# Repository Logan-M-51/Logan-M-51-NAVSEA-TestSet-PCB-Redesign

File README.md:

# Logan-M-51-NAVSEA-TestSet-PCB-Redesign
This project was completed as a senior design project as one of the graduation requirements for the Computer Engineering and Systems
program at the university of Washington Tacoma. 
This particular project was sponsored by NAVSEA, and completed with a group of three students.

This assignment was given to UWT students to extend the lifespan of the detonator test set circuitry shelf life. 
The current solution is over half a century old and is experiencing more failures as time goes on.
Thus, this redesign mimics the same functionality of the original test set while in a PCB format.
This allows NAVSEA engineers to replace the components in use withouth having to retrain test set operators.

Solution was tested in LTSpice, as well as on breadboard recreations.

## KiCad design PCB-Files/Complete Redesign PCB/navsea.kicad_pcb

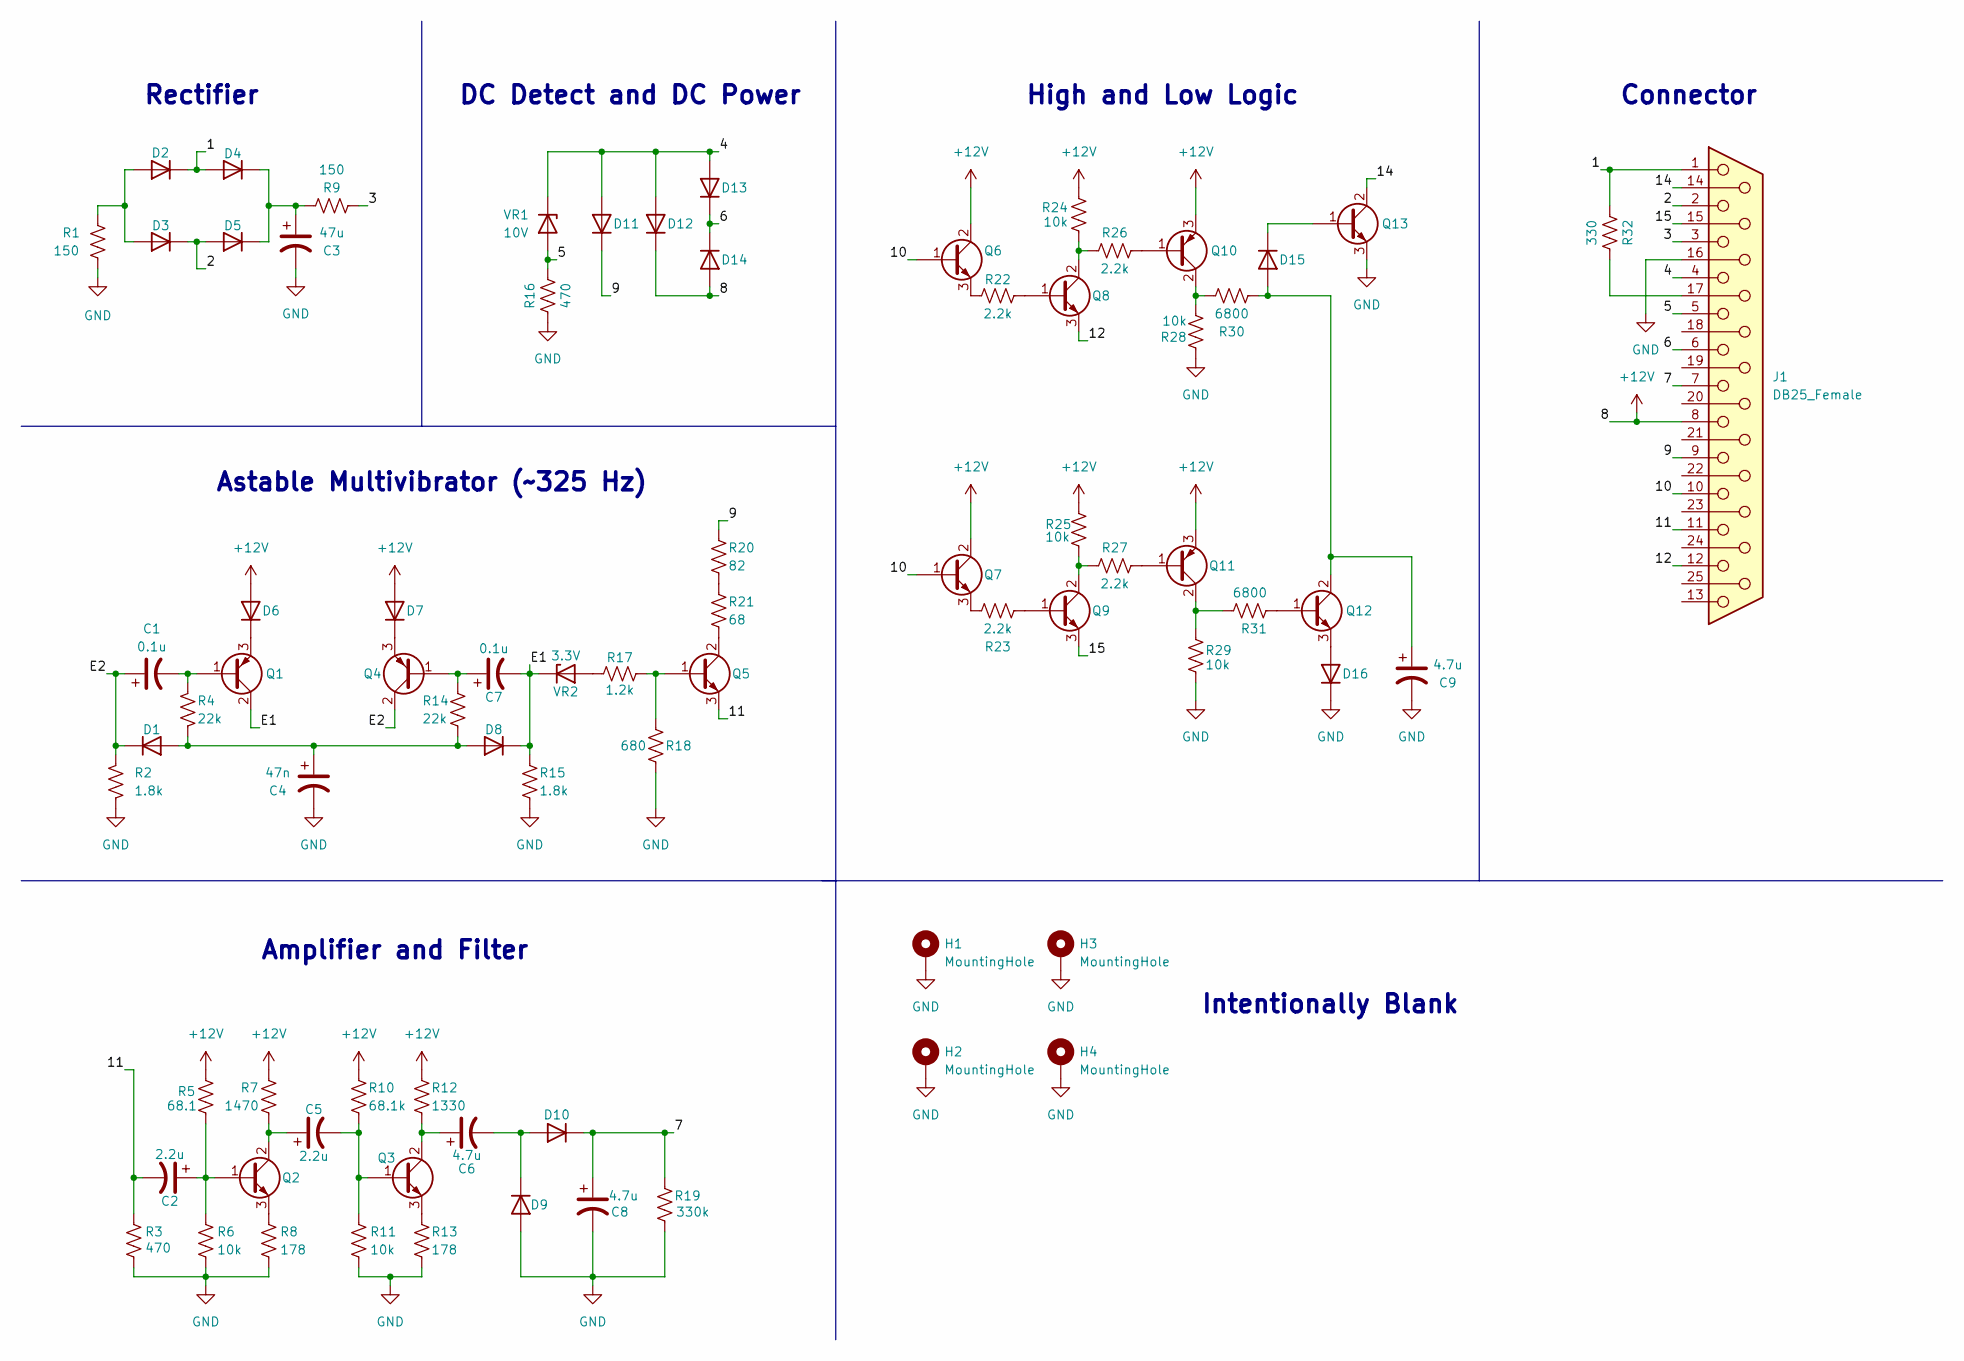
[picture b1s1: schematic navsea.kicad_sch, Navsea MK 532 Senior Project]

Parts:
C1, C7: 0.1u; CP_Radial_Tantal_D4.5mm_P2.50mm
C2, C5: 2.2u; CP_Radial_Tantal_D4.5mm_P2.50mm
C3: 47u; CP_Radial_D8.0mm_P3.50mm
C4: 47n; C_Axial_L5.1mm_D3.1mm_P10.00mm_Horizontal
C6: 4.7u; CP_Radial_D8.0mm_P3.50mm
C8, C9: 4.7u; CP_Axial_L10.0mm_D4.5mm_P15.00mm_Horizontal
D1, D2, D3, D4, D5, D6, D7, D8, D9, D10, D11, D12, D13, D14, D15, D16: D; D_DO-41_SOD81_P7.62mm_Horizontal
H1, H2, H3, H4: MountingHole; MountingHole_4.3mm_M4_Pad_Via
J1: DB25_Female; DSUB-25_Female_Horizontal_P2.77x2.84mm_EdgePinOffset4.94mm_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
Q1, Q4, Q10, Q11: PNP; TO-18-3
Q2, Q3, Q5, Q6, Q7, Q8, Q9, Q12, Q13: Q_NPN_BCE; TO-18-3
R1, R9: 150; R_Axial_DIN0414_L11.9mm_D4.5mm_P15.24mm_Horizontal
R2, R15: 1.8k; R_Axial_DIN0207_L6.3mm_D2.5mm_P7.62mm_Horizontal
R3, R16: 470; R_Axial_DIN0207_L6.3mm_D2.5mm_P7.62mm_Horizontal
R4, R14: 22k; R_Axial_DIN0207_L6.3mm_D2.5mm_P7.62mm_Horizontal
R5: 68.1; R_Axial_DIN0207_L6.3mm_D2.5mm_P7.62mm_Horizontal
R6, R11, R24, R25, R28, R29: 10k; R_Axial_DIN0207_L6.3mm_D2.5mm_P7.62mm_Horizontal
R7: 1470; R_Axial_DIN0207_L6.3mm_D2.5mm_P7.62mm_Horizontal
R8, R13: 178; R_Axial_DIN0207_L6.3mm_D2.5mm_P7.62mm_Horizontal
R10: 68.1k; R_Axial_DIN0207_L6.3mm_D2.5mm_P7.62mm_Horizontal
R12: 1330; R_Axial_DIN0207_L6.3mm_D2.5mm_P7.62mm_Horizontal
R17: 1.2k; R_Axial_DIN0207_L6.3mm_D2.5mm_P7.62mm_Horizontal
R18: 680; R_Axial_DIN0207_L6.3mm_D2.5mm_P7.62mm_Horizontal
R19: 330k; R_Axial_DIN0207_L6.3mm_D2.5mm_P7.62mm_Horizontal
R20: 82; R_Axial_DIN0207_L6.3mm_D2.5mm_P7.62mm_Horizontal
R21: 68; R_Axial_DIN0207_L6.3mm_D2.5mm_P7.62mm_Horizontal
R22, R23, R26, R27: 2.2k; R_Axial_DIN0207_L6.3mm_D2.5mm_P7.62mm_Horizontal
R30, R31: 6800; R_Axial_DIN0207_L6.3mm_D2.5mm_P7.62mm_Horizontal
R32: 330; R_Axial_DIN0207_L6.3mm_D2.5mm_P7.62mm_Horizontal
VR1: 10V; D_DO-41_SOD81_P7.62mm_Horizontal
VR2: 3.3V; D_DO-35_SOD27_P7.62mm_Horizontal

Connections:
+12V: D6.2 (A), D7.2 (A), D12.1 (K), D14.2 (A), J1.8, Q6.2 (C), Q7.2 (C), Q10.3 (E), Q11.3 (E), R5.1, R7.1, R10.1, R12.1, R24.1, R25.1
/1: D2.1 (K), D4.2 (A), J1.1, R32.2
/2: D3.1 (K), D5.2 (A), J1.2
/3: J1.3, R9.1
/4: D11.2 (A), D12.2 (A), D13.2 (A), J1.4, VR1.1 (K)
/5: J1.5, R16.2, VR1.2 (A)
/6: D13.1 (K), D14.1 (K), J1.6
/7: C8.1, D10.1 (K), J1.7, R19.1
/9: D11.1 (K), J1.9, R20.1
/10: J1.10, Q6.1 (B), Q7.1 (B)
/11: C2.2, J1.11, Q5.3 (E), R3.1
/12: J1.12, Q8.3 (E)
/14: J1.14, Q13.2 (C)
/15: J1.15, Q9.3 (E)
/E1: C7.2, D8.1 (K), Q1.2 (C), R15.1, VR2.1 (K)
/E2: C1.1, D1.1 (K), Q4.2 (C), R2.1
GND: C3.2, C4.2, C8.2, C9.2, D9.2 (A), D16.1 (K), H1.1, H2.1, H3.1, H4.1, J1.16, Q13.3 (E), R1.2, R2.2, R3.2, R6.2, R8.2, R11.2, R13.2, R15.2, R16.1, R18.1, R19.2, R28.2, R29.2
unnamed: C1.2, Q1.1 (B), R4.1
unnamed: C2.1, Q2.1 (B), R5.2, R6.1
unnamed: C3.1, D4.1 (K), D5.1 (K), R9.2
unnamed: C4.1, D1.2 (A), D8.2 (A), R4.2, R14.2
unnamed: C5.1, Q2.2 (C), R7.2
unnamed: C5.2, Q3.1 (B), R10.2, R11.1
unnamed: C6.1, Q3.2 (C), R12.2
unnamed: C6.2, D9.1 (K), D10.2 (A)
unnamed: C7.1, Q4.1 (B), R14.1
unnamed: C9.1, D15.2 (A), Q12.2 (C), R30.1
unnamed: D2.2 (A), D3.2 (A), R1.1
unnamed: D6.1 (K), Q1.3 (E)
unnamed: D7.1 (K), Q4.3 (E)
unnamed: D15.1 (K), Q13.1 (B)
unnamed: D16.2 (A), Q12.3 (E)
unnamed: J1.17, R32.1
unnamed: Q2.3 (E), R8.1
unnamed: Q3.3 (E), R13.1
unnamed: Q5.1 (B), R17.2, R18.2
unnamed: Q5.2 (C), R21.2
unnamed: Q6.3 (E), R22.1
unnamed: Q7.3 (E), R23.1
unnamed: Q8.1 (B), R22.2
unnamed: Q8.2 (C), R24.2, R26.1
unnamed: Q9.1 (B), R23.2
unnamed: Q9.2 (C), R25.2, R27.1
unnamed: Q10.1 (B), R26.2
unnamed: Q10.2 (C), R28.1, R30.2
unnamed: Q11.1 (B), R27.2
unnamed: Q11.2 (C), R29.1, R31.1
unnamed: Q12.1 (B), R31.2
unnamed: R17.1, VR2.2 (A)
unnamed: R20.2, R21.1

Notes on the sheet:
Rectifier
Connector
DC Detect and DC Power
Amplifier and Filter
Intentionally Blank
High and Low Logic
Astable Multivibrator (~325 Hz)

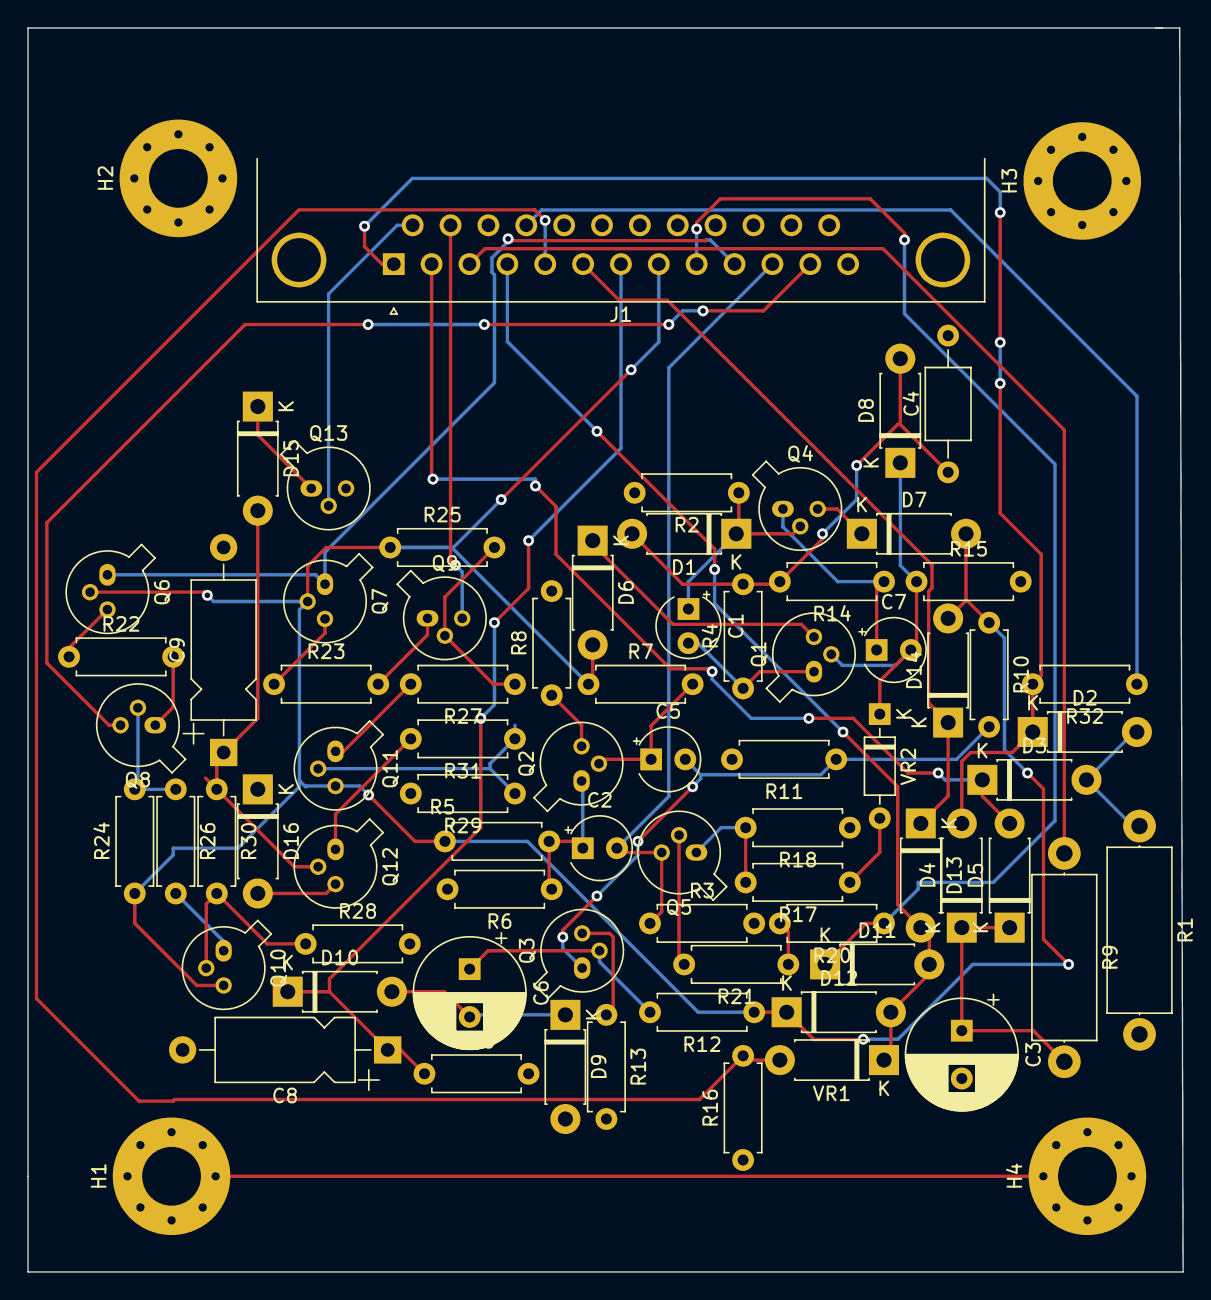
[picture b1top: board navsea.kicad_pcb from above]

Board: 2 copper layers, 84.5 x 91.0 mm, 77 parts (0 on the bottom side), 50 nets.
